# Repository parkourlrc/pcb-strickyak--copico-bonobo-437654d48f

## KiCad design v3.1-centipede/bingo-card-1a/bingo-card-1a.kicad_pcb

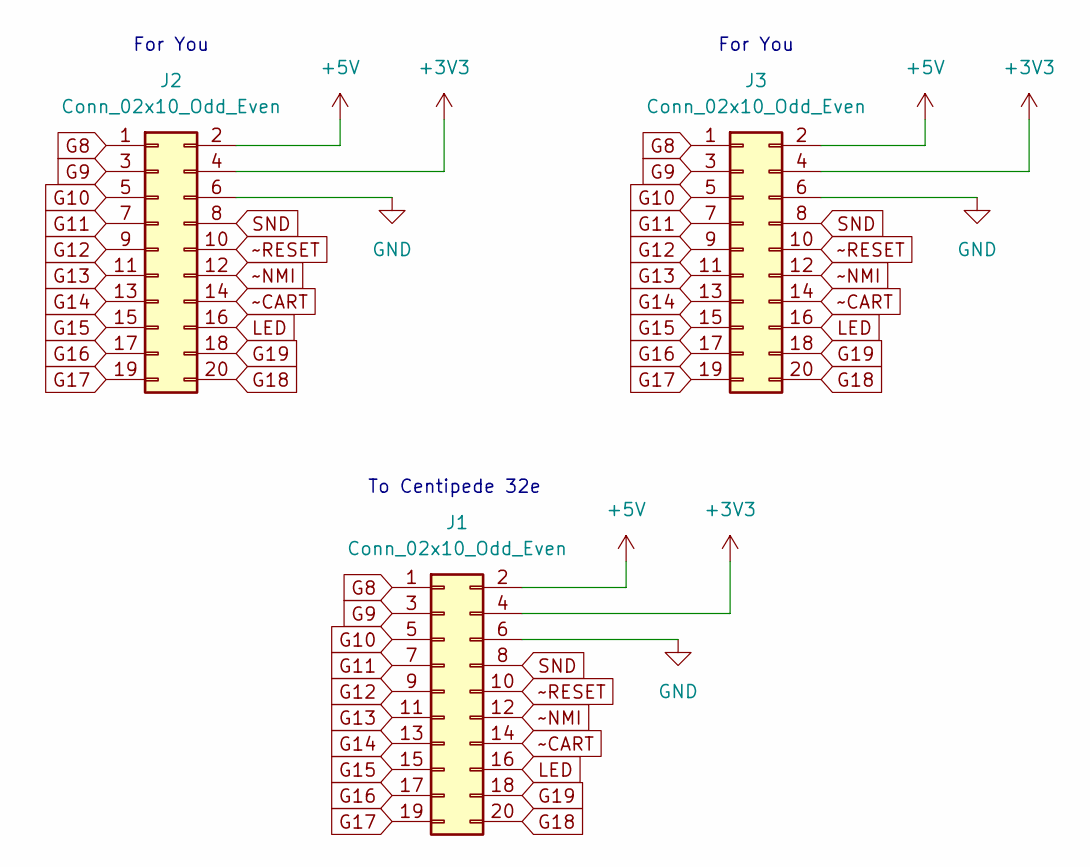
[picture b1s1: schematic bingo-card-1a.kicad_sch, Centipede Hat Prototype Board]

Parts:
J1, J2, J3: Conn_02x10_Odd_Even; PinHeader_2x10_P2.54mm_Vertical

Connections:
+3V3: J1.4, J2.4, J3.4
+5V: J1.2, J2.2, J3.2
G8: J1.1, J2.1, J3.1
G9: J1.3, J2.3, J3.3
G10: J1.5, J2.5, J3.5
G11: J1.7, J2.7, J3.7
G12: J1.9, J2.9, J3.9
G13: J1.11, J2.11, J3.11
G14: J1.13, J2.13, J3.13
G15: J1.15, J2.15, J3.15
G16: J1.17, J2.17, J3.17
G17: J1.19, J2.19, J3.19
G18: J1.20, J2.20, J3.20
G19: J1.18, J2.18, J3.18
GND: J1.6, J2.6, J3.6
LED: J1.16, J2.16, J3.16
SND: J1.8, J2.8, J3.8
~CART: J1.14, J2.14, J3.14
~NMI: J1.12, J2.12, J3.12
~RESET: J1.10, J2.10, J3.10

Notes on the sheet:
For You
To Centipede 32e

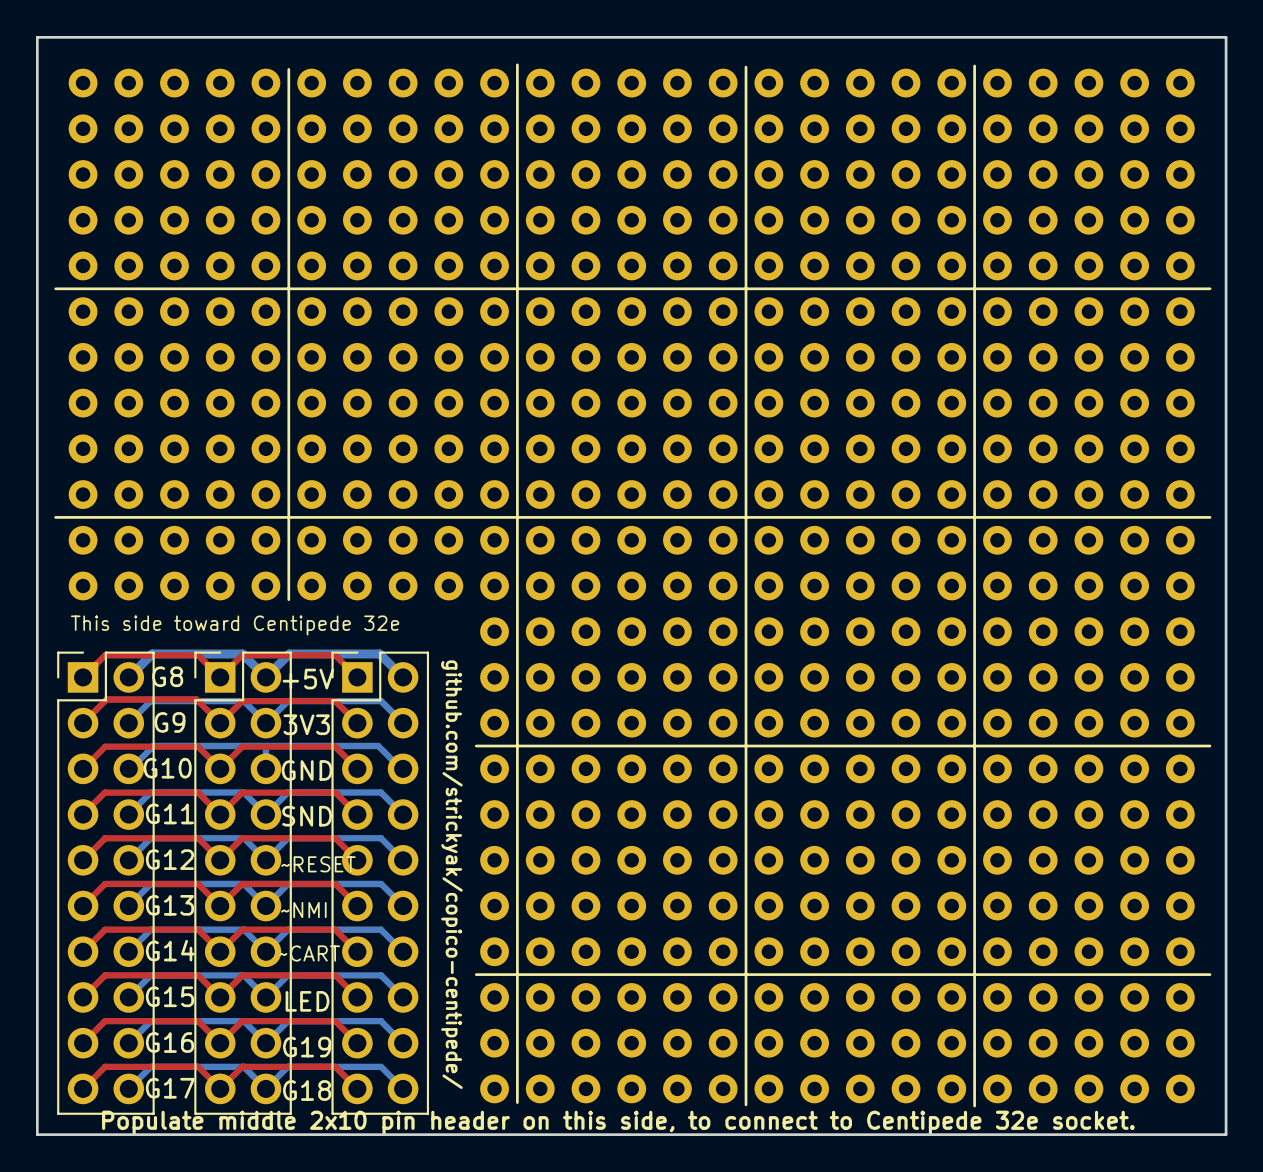
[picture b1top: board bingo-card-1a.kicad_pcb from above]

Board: 2 copper layers, 66.0 x 61.0 mm, 3 parts (0 on the bottom side), 20 nets.

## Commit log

2026-04-19 hat-fuji-40c
2026-04-19 Gerbers-bingo-card-1a for Centipede
